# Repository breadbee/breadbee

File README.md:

# Breadbee

A very small, 32mm x 30mm, ARM Cortex A7 development board that costs about ~$10
to make in low quantities and can be assembled at home with a cheap hot air rework
station. With a [small adapter socket](./hivee) it can be mounted vertically in a standard breadboard.

The breadbee is based on a relatively unknown IP camera SoC, the MSC313E, from a company called MStar
(now part of MediaTek as a subsidiary called SigmaStar).
You might have never heard of MStar but you probably have one of their chips in your TV.

## Features

These are features that are working:

- ~1GHz Cortex A7 CPU with NEON etc[0].
- 64MB DDR2 (Probably DDR2-1333)
- 128KB SRAM (88KB if you use a MSC313(no e).
- [Bootable, memory mapped SPI-NOR](https://github.com/fifteenhex/linux/blob/msc313e/drivers/spi/spi-msc313-isp.c)
- 100Mbit ethernet.
- [4 x 10bit ADC channels](https://github.com/fifteenhex/linux/blob/msc313e/drivers/iio/adc/msc313e_sar.c)
- [2 x SPI](https://github.com/fifteenhex/linux/blob/msc313e/drivers/spi/spi-msc313.c)
- [1 x I2C (there is possibly one more)](https://github.com/fifteenhex/linux/blob/msc313e/drivers/i2c/busses/i2c-msc313e.c)
- [3 UARTs](https://github.com/fifteenhex/linux/blob/b3c521f8f30c9cc6f9f9c5c87429336d4756dcca/drivers/tty/serial/8250/8250_dw.c#L751) [1]
- Lots of GPIO. At least one pin with wake up support.
- [RTC](https://github.com/fifteenhex/linux/blob/msc313e/drivers/rtc/rtc-msc313e.c)
- [WDT](https://github.com/fifteenhex/linux/blob/msc313e/drivers/watchdog/msc313e_wdt.c)
- [3 x Timer](https://github.com/fifteenhex/linux/blob/msc313e/drivers/clocksource/timer-msc313e.c)
- [8 x PWM](https://github.com/fifteenhex/linux/blob/msc313e/drivers/pwm/pwm-msc313e.c)
- [SD/SDIO interface](https://github.com/fifteenhex/linux/blob/msc313e/drivers/mmc/host/mstar-fcie.c)
- 2 x ["byte" dma controller](https://github.com/fifteenhex/linux/blob/msc313e/drivers/dma/mstar/mstar-msc313-bdma.c)
- USB PHY
- USB host/device mux
- Faraday FUSBH200 USB *ehci* host controller
- On die temperature sensor. (sorta)
- Hardware RNG. (quality unknown)
- SHA engine. (Runs, not wired to the kernel)
- 8051 "house keeping" MCU. (Basic remoteproc driver)

[0] MStar says it's 800MHz but their own cpufreq code says they clock it to 1GHz
Clocking up to 1.1GHz works fine running dhrystone for hours but causes random lock ups if the spi nor controller and ethernet are fighting for bus access.
[1] One UART is used by the serial console, two more are available via muxing. 

 The chip has a bunch of stuff in it that isn't supported yet:
 - [MUSB USB device controller](https://github.com/fifteenhex/linux/blob/msc313e/drivers/usb/musb/mstar.c)
 - Camera interface, h264 encoder, mjpeg etc.
 - Audio ADC/DAC
 - [Crypto engine](https://github.com/fifteenhex/linux/blob/msc313e/drivers/crypto/msc313-aesdma.c) that seems to be able to do AES encrypted DMA transfers, memory mapped AES encryption etc
 - Some sort of IR decoder that can wake the chip up based on the IR codes it sees.
 - 6 byte unique device ID and efuse for key storage
 - [command queue dma controller](https://github.com/fifteenhex/linux/blob/msc313e/drivers/dma/mstar/mstar-msc313-cmdq.c)

It's full of flashy magic!

## Power consumption

According to a Kyoritsu KEW 1062 inline with the vbus of a usb cable:

| state        | Ethernet on | RTC wake | value |
|--------------|-------------|----------|-------|
| Booted idle  | yes         | N/A      | 138mA |
| Booted idle  | no          | N/A      | 113mA |
| Memory sleep |             | Yes      | 12mA  |

## Board Revisions

- Rev0 - Original version, works.
- Rev1 - Same as rev0 basically but the QFN80 footprint is slightly fixed to not have very thin pads on one side. Rev1 has one weird pad on the QFN80 footprint and an overlapping extra trace on one of the USB signals.

## Motivations

- Networked microcontrollers are a disaster waiting to happen; Many solutions - even commercial ones - use LWIP as the TCP/IP stack with no intention of actually maintaining it, use relatively unknown TLS libraries because of lack of memory, have no memory protection, no isolation between the moving parts.

- There are no solutions yet that can run a real OS like Linux that can be integrated by hobbyists into boards from cheap PCB vendors that don't have show stopping limitations. I.e. the AllWinner V3s is very similar to the SoC used here but it only has one SPI controller that is lost as soon as you put SPI NOR on it. The MSC313E has just enough of the usual microcontroller peripherals to make it useful, comes in a (relatively) easy to work with QFN package, is tiny and costs ~$4.
It is a bit harder to integrate into your designs than a microcontroller that requires a single power supply but all of the information you would need to do so is right here. The schematic for the breadbee is incredibly simple.

- There are single board computers out there that have more cores, more memory etc and are still around $10 but they are over kill for applications where even an ESP32 has enough horse power and they aren't usually something you can integrate into your project without reserving considerable space.

- Why not? The MSC313E is a Cortex-A so getting Linux running from scratch was relatively simple. The peripherals are super weird in places but not totally insane.

## But where's the WiFi!>!!111

The breadbee is meant to be a "minimum viable product" to get the ball rolling. It's impossible to write drivers for the SDIO controller or USB needed for WiFi without a platform to work on. Breadbee is that platform. Once SDIO works there will be an Ampak AP6212 based module to add wifi to breadbees and maybe a respin of the breadbee with the ethernet jack replaced with an Ampak module. 

A simpler alternative consists in using an already supported USB-to-WiFi PCB module given that the breadbee's USB host controller already works fine. This project is .

## Can I have one.. where do I get the chips..

- If you ask very nicely and you are willing to do something like write a nice python library or flesh out drivers for the board it's possible you can have one of the prototype boards for FREE! Get in touch!

- ~~If you just want to buy one the intention is to put the board up on a crowd sourcing site at some point. When that happens that information will be here.~~ [crowdsupply](https://www.crowdsupply.com/daniel-palmer/breadbee) will eventually be selling premade boards. This might take a while though.

- If you want chips to integrate into your own projects and don't have contacts in Shenzhen to get them get in touch and we'll figure something out. If you want 2080 of them getting them isn't a problem. If you want one or two I have a small supply. If the crowd sourcing happens and there is enough money left to buy extra chips to distribute in more accessible ways I will. Since April 2020 chips have now also started to turn on up ebay.

- The gerbers have been uploaded to [OSH park (rev1)](https://oshpark.com/shared_projects/lQ6wt3Dk) ready to order. [OSH park (rev0)](https://oshpark.com/shared_projects/slorKWK0)

## Software

Note that this is all in flux right at the moment. These repos are getting rebase'd fairly often.

### U-boot

There is a basic port of u-boot that so far take over from the MStar IPL and load a kernel from the SPI NOR, write it etc.
See boot process below for more details.

https://github.com/fifteenhex/u-boot/tree/msc313

### Kernel

All of the above features work to some degree in the work tree. Mainlining is in progress but will take time.
For more info please see the linux-chenxing.org [page about mainlining](http://linux-chenxing.org/mainlining.html).

### Buildroot

Combines the u-boot and kernel above with a root filesystem and generates flashable images.
There are some small pieces of a board configuration application called "beecfg" to setup pinmuxing etc.

https://github.com/fifteenhex/breadbee_buildroot

## BoM

[Google Sheet](https://docs.google.com/spreadsheets/d/1FwoQdfAULd6vKPnkrVnFDfQQs8OdsqdwefH3aLVehPo)

## Pin Table

### J2 - Main 2.54mm header

| interrupt | 5v tolerant |   notes   | alt functions           |    name   |  # |  # |   name    | alt functions           |   notes                 | 5v tolerant | interrupt |
|-----------|-------------|-----------|-------------------------|-----------|----|----|-----------|-------------------------|-------------------------|-------------|-----------|
|           |             |           |                         |    +5v    |  1 | 2  |   +3v3    |                         |                         |             |           |
|           |             |           |                         |    gnd    |  3 | 4  | pm_gpio4  |                         | [0]                     |    yes      |   yes     |
|           |             |           |                         | i2c1_scl  |  5 | 6  | i2c1_sda  |                         |                         |             |           |
|   yes     |             |           | ej_tck, pwm4            | spi0_cz   |  7 | 8  | spi0_ck   | ej_tms, pwm5            |                         |             |   yes     |
|   yes     |             |           | ej_tdo, pwm6            | spi0_di   |  9 | 10 | spi0_do   | ej_tdi, pwm7            |                         |             |   yes     |
|           |     yes     |           |                         | sar_gpio2 | 11 | 12 | sar_gpio3 |                         |                         |    yes      |           |
|           |     yes     |           |                         | sar_gpio1 | 13 | 14 | sar_gpio0 |                         |                         |    yes      |           |
|           |     yes     |   cs      | spi0_cz, pwm0           | fuart_rx  | 15 | 16 | fuart_tx  | spi0_ck, pwm1           |   clk                   |    yes      |           |
|           |     yes     | mosi, [1] | spi0_di, pwm2, uart1_rx | fuart_cts | 17 | 18 | fuart_rts | spi0_do, pwm3, uart1_tx |   miso                  |    yes      |           |
|           |             |           |                         | sr_io7    | 19 | 20 | sr_io6    |                         |                         |             |           |
|           |             |           |                         | sr_io5    | 21 | 22 | sr_io4    |                         |                         |             |           |
|           |             |           |                         | sr_io3    | 23 | 24 | sr_io2    |                         |                         |             |           |

0: This is a special pin that has to be explictly unlocked to be set. It seems to be intended for powering down the main CPU. It might move on rev1.

1 - When fuart is mux'd in it's also possible to mux'in uart1 and get a working rx only
    second uart here.

### J4 - Misc/High speed interfaces

* Note the USB and SD/SDIO are not guaranteed to work as literally no care was taken to route those signals properly on rev0. 

| name      | #  | alt functions | 5v tolerant | interrupt | notes |
|-----------|----|---------------|-------------|-----------|-------|
| +3v3      | 1  |               |             |           |       |
| sd_d3     | 2  |   spi1_do     | yes         |           | miso  |
| sd_d2     | 3  |   spi1_di     | yes         |           | mosi  |
| sd_d1     | 4  |   spi1_ck     | yes         |           | clk   |
| sd_d0     | 5  |   spi1_cz     | yes         |           | cs    |
| sd_cmd    | 6  |               | yes         |           |       |
| sd_clk    | 7  |               | yes         |           |       |
| pm_sd_cdz | 8  |               |             | yes       |       |
| gnd       | 9  |               |             |           |       |
| +5v       | 10 |               |             |           |       |
| usb_dm    | 11 |               |             |           |       |
| usb_dp    | 12 |               |             |           |       |
| gnd       | 13 |               |             |           |       |
| sr_io15   | 14 |               |             |           |       |
| sr_io14   | 15 |               |             |           |       |
| sr_io13   | 16 |               |             |           |       |
| sr_io12   | 17 |               |             |           |       |
| sr_io11   | 18 |               |             |           |       |
| sr_io10   | 19 |               |             |           |       |
| sr_io9    | 20 |               |             |           |       |
| sr_io8    | 21 |               |             |           |       |

### Test Points

- The audio pins are broken out to a series of test points on the left side of the parts size of the board.
- pm_irin is broken out to a test point on the ethernet jack side of the board.

## Using JTAG

JTAG is enabled at boot up on the spi0 pins by the u-boot SPL.

## More technical info

[linux-chenxing](http://linux-chenxing.org) has more info about mstar/sigmastar socs.

## Articles etc

[A nice blog entry from Willy about his experience building boards](https://wtarreau.blogspot.com/2020/09/breadbee-build-your-own-single-board.html)

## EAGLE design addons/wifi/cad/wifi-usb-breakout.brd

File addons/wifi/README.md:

# How to simply add WiFi to a breadbee

This is far from being of high quality, but provided little effort, it is possible to add a simple WiFi module to the breadbee.

There are a wide variety of cheap USB modules provided as a small 12.3x13mm PCB with 4 pins on one side and 2 on the other one. These modules work from 3.3V and are connected via USB. Usually they do not have any antenna but one can be connected to the two pins on one side.

Such modules are widely used in WiFi cameras and various consumer appliances, and are usually available from $1.50 to $5.00 depending on the modules. Just search for RTL8188EUS, RTL8188ETV, RTL8188FTV, MT7601U to find a few such devices. Most of them use the exact same footprint and pinout.

The breadbee board features a USB 2.0 controller with a port accessible on the J4 connector:

Pin |  Function
----|-----------
  1 |   +3.3V
 11 |   USB-DM
 12 |   USB-DP
 13 |   GND

Modules which contain a connector can be directly connected to these pins using 4 wires, as shown below:

In order to get a cleaner assembly, it is recommended instead to build a breakout board for the module. This is what is proposed in this directory.

The board was designed using Eagle CAD, for which the files are available in the  but the schematic and board layout are also provided as PDF and PNG in the . The board contains a PCB-printed antenna. These antennas can be efficient but are quite complex to design because they depend on the PCB's material and thickness, and the surrounding metal parts. There is a widely available literature on the subject but given the author had no experience there, a first quick-and-dirty attempt was made, losely inspired by the following documents after carefully studying them, and taking into account the constraints of the PCB's size and the fact that the one used here was single-sided:
 - https://www.nxp.com/docs/en/nxp/application-notes/AN11994.pdf
 - http://www.idc-online.com/technical_references/pdfs/electrical_engineering/A%20Highly%20Reliable%20Platform.pdf
 - https://www.cypress.com/documentation/application-notes/an91445-antenna-design-and-rf-layout-guidelines
 - https://www.autodesk.com/products/eagle/blog/everyday-app-note-design-efficient-antenna-rf-layout/
 - https://e2e.ti.com/support/wireless-connectivity/bluetooth/f/538/t/626343?CC2640R2F-Need-Smaller-BLE-2-4G-antenna-TI-design

The board was made using cheap 1.6mm FR4 PCB and provided great results (mesured as the ability to connect and maintain a correct TCP transfer rate at a given distance). Without any antenna, such boards barely connect more than 5-10 meters away on the same floor. With the PCB's antenna, it was possible to maintain roughly 20-25 Mbps between two different stairs.

It is important to make sure the board will be printed to the appropriate dimensions: the J4 connector has a 1mm pitch, and even a 1% error would cause 0.1mm error over 1cm and could be an issue to connect the pins while keeping the boards perfectly tight. It is wise to verify the alignment when drilling the 4 holes (0.4 to 0.5mm max):

Then the board may completely cover the J4 connector to keep wires short:

The module just needs to be soldered on 6 points. It's recommended to make sure that no contact may be made against the ground plane underneath the module. In case of doubt, a small piece of Kapton tape may be placed between the two, or the module can be kept slightly elevated during soldering.

The resulting assembly can then be pressed against the breadbee and connected using resistor tails. Alternately, it may be placed on top of the RJ45 connector using short wires. It would also be possible to place it on the SoC side, but in this case it is important to be very careful about insulation.

# Testing the board

First, the kernel needs to enable the UHCI controller. For this, a uhci0 DTB overlay should be used. The author doesn't know how to use overlays, so instead the following patch was applied to the DTS:

```
diff --git a/arch/arm/boot/dts/infinity3-msc313e-breadbee.dts b/arch/arm/boot/dts/infinity3-msc313e-breadbee.dts>
index d7445db8a388..8f5d111baca7 100644
--- a/arch/arm/boot/dts/infinity3-msc313e-breadbee.dts
+++ b/arch/arm/boot/dts/infinity3-msc313e-breadbee.dts
@@ -24,3 +24,7 @@ chosen {
 &pm_uart {
 	status = "okay";
 };
+
+&uhc0 {
+	status = "okay";
+};

```

From this point, the USB controller should be enumerated with its I/O memory address:
```
# dmesg | grep hcd
[    0.921383] fotg210_hcd: FOTG210 Host Controller (EHCI) Driver
[    0.934328] fotg210-hcd 1f284800.uhc: Faraday USB2.0 Host Controller
[    0.940675] fotg210-hcd 1f284800.uhc: new USB bus registered, assigned bus number 1
[    0.948413] fotg210-hcd 1f284800.uhc: irq 48, io mem 0x1f284800
[    0.962221] fotg210-hcd 1f284800.uhc: USB 2.0 started, EHCI 1.00
[    1.397675] usb 1-1: new high-speed USB device number 2 using fotg210-hcd
[   15.032213] usb 1-1: reset high-speed USB device number 2 using fotg210-hcd
```

Using `usb-devices` it should be possible to enumerate the device:

```
# /etc/bin/usb-devices 

T:  Bus=01 Lev=00 Prnt=00 Port=00 Cnt=00 Dev#=  1 Spd=480 MxCh= 1
D:  Ver= 2.00 Cls=09(hub  ) Sub=00 Prot=01 MxPS=64 #Cfgs=  1
P:  Vendor=1d6b ProdID=0002 Rev=05.08
S:  Manufacturer=Linux 5.8.1-bbw fotg210_hcd
S:  Product=Faraday USB2.0 Host Controller
S:  SerialNumber=1f284800.uhc
C:  #Ifs= 1 Cfg#= 1 Atr=e0 MxPwr=0mA
I:  If#=0x0 Alt= 0 #EPs= 1 Cls=09(hub  ) Sub=00 Prot=00 Driver=hub

T:  Bus=01 Lev=01 Prnt=01 Port=00 Cnt=01 Dev#=  2 Spd=480 MxCh= 0
D:  Ver= 2.01 Cls=00(>ifc ) Sub=00 Prot=00 MxPS=64 #Cfgs=  1
P:  Vendor=148f ProdID=7601 Rev=00.00
C:  #Ifs= 1 Cfg#= 1 Atr=80 MxPwr=160mA
I:  If#=0x0 Alt= 0 #EPs= 8 Cls=ff(vend.) Sub=ff Prot=ff Driver=mt7601u
```

Note that this is with an MT7601U board above. An RTL8188 will likely show something different. If this works, we can go on with enabling WiFi client support in the kernel.

# Enabling WiFi support in the kernel

The following config options were added on top of a kernel 5.8 config that was operational for the breadbee board. Note that we're speaking about the breadbee development tree, not yet 100% mainline. Only MT7601 was added there. Another option is available for RTL8188, but was not tested (look for `R8188EU`).

```
CONFIG_SYSTEM_DATA_VERIFICATION=y
CONFIG_ASN1=y
CONFIG_WIRELESS=y
CONFIG_CFG80211=y
CONFIG_CFG80211_REQUIRE_SIGNED_REGDB=y
CONFIG_CFG80211_USE_KERNEL_REGDB_KEYS=y
CONFIG_CFG80211_CRDA_SUPPORT=y
CONFIG_MAC80211=m
CONFIG_MAC80211_HAS_RC=y
CONFIG_MAC80211_RC_MINSTREL=y
CONFIG_MAC80211_RC_DEFAULT_MINSTREL=y
CONFIG_MAC80211_RC_DEFAULT="minstrel_ht"
CONFIG_MAC80211_LEDS=y
CONFIG_MAC80211_STA_HASH_MAX_SIZE=0
CONFIG_FW_LOADER_PAGED_BUF=y
CONFIG_EXTRA_FIRMWARE="mt7601u.bin"
CONFIG_EXTRA_FIRMWARE_DIR="/lib/firmware"
CONFIG_FW_LOADER_USER_HELPER=y
CONFIG_WLAN=y
CONFIG_WLAN_VENDOR_MEDIATEK=y
CONFIG_MT7601U=m
CONFIG_KEYS=y
CONFIG_CRYPTO_AEAD=m
CONFIG_CRYPTO_AKCIPHER=y
CONFIG_CRYPTO_GF128MUL=m
CONFIG_CRYPTO_NULL=m
CONFIG_CRYPTO_RSA=y
CONFIG_CRYPTO_CCM=m
CONFIG_CRYPTO_GCM=m
CONFIG_CRYPTO_CTR=m
CONFIG_CRYPTO_CMAC=m
CONFIG_CRYPTO_GHASH=m
CONFIG_CRYPTO_HASH_INFO=y
CONFIG_CRYPTO_LIB_ARC4=m
CONFIG_ASYMMETRIC_KEY_TYPE=y
CONFIG_ASYMMETRIC_PUBLIC_KEY_SUBTYPE=y
CONFIG_X509_CERTIFICATE_PARSER=y
CONFIG_PKCS7_MESSAGE_PARSER=y
CONFIG_SYSTEM_TRUSTED_KEYRING=y
CONFIG_SYSTEM_TRUSTED_KEYS=""
CONFIG_ASSOCIATIVE_ARRAY=y
CONFIG_CLZ_TAB=y
CONFIG_MPILIB=y
CONFIG_OID_REGISTRY=y
```

The MT7601U driver requires a firmware (`mt7601u.bin`). As there was no convenient place to store this firmware in the image, it was simply embedded in the kernel and retrieved from /lib/firmware on the build host.

Once rebuilt with these options, the kernel may be booted again and the module loaded:

```
# modprobe mt7601u
# lsmod
Module                  Size  Used by
mt7601u                45056  -2
mac80211              274432  -2
libarc4                16384  -2
```

Note the use count of -2 which was not yet diagnosed. Either it results from one of the module options to explicitly prevent from unloading the module, or it's a bug. As such if a new module option is needed, one needs to reboot the board and try again. Regardless, once the module is loaded, it works pretty fine.

# Building a stripped down wpa_supplicant

If one wants to connect to a WPA-protected network (which is very likely), the `wpa_supplicant` utility will be needed. This one will usually be huge by default as it supports a lot of protocols and options. However it also supports disabling many of them to reduce its footprint. It may be configured this way:

```
$ printf \
        "CONFIG_DRIVER_NL80211=y\n"             \
        "CONFIG_READLINE=y\n"                   \
        "CONFIG_NO_STDOUT_DEBUG=y\n"            \
        "CONFIG_NO_SCAN_PROCESSING=y\n"         \
        "CONFIG_BACKEND=file\n"                 \
        "CONFIG_NO_CONFIG_WRITE=y\n"            \
        "CONFIG_NO_CONFIG_BLOBS=y\n"            \
        "CONFIG_NO_LINUX_PACKET_SOCKET_WAR=y\n" \
        "CONFIG_IEEE80211W=y\n"                 \
        "CONFIG_NO_RANDOM_POOL=y\n"             \
        "CONFIG_GETRANDOM=y\n"                  \
        "CONFIG_IEEE80211N=y\n"                 \
        "CONFIG_IEEE80211AC=y\n"                \
        "CONFIG_NO_ROAMING=y\n"                 \
        "CONFIG_IBSS_RSN=y\n"                   \
        > wpa_supplicant/.config

$ CC=/path/to/cross-compiler LD='$(CC)' CFLAGS="-MMD -Os" \
  make -j$(nproc) -C wpa_supplicant
```

The development version of openssl and libnl will have to be installed in the sysroot. The resulting binary is still large (~300 kB) but compresses well in a squashfs (~120 kB).

A minimal config file like this one is sufficient:

```
# cat /etc/wpa_supplicant-wlan0.conf
network={
 ssid="lab-test"
 scan_ssid=1
 key_mgmt=WPA-PSK
 proto=WPA RSN
 psk="Lab-Test-Passw0rd"
}
```

Starting wpa_supplicant with the wlan0 interface using this config should now work:

```
# wpa_supplicant -B -iwlan0 -c/etc/wpa_supplicant-wlan0.conf -P/var/run/wpa_supplicant-wlan0.pid
# iw dev
phy#0
 Interface wlan0
   ifindex 3
   wdev 0x1
   addr 00:0c:43:12:34:56
   ssid lab-test
   type managed
   channel 7 (2442 MHz), width: 40 MHz, center1: 2452 MHz
   txpower 20.00 dBm

```

Once this is done, the wlan0 interface should appear as `UP` and an address may be retrieved using dhcpcd:

```
# ip li show dev wlan0
3: wlan0: <BROADCAST,MULTICAST,UP,LOWER_UP> mtu 1500 qdisc mq state UP mode DORMANT group default qlen 1000
    link/ether 00:0c:43:12:34:56 brd ff:ff:ff:ff:ff:ff
```

From now on, everything is specific to the distro in use.

# Final words

It's very easy to add such a module that might be salvaged from a dead camera (like the one used above), and the breadbee has the excellent taste of placing the pins in the same order as the module's so there's no risk of getting anything wrong. The breakout board is not strictly required, a previous successful attempt was made using 3cm wires on both the `ANT` and `GND` pins that were bent over the RJ45 connector. As a side note, this howto was written with dumps retrieved from the breadbee over Wifi! Try it, it's easy and fun. You won't look at your ESP32 the same way after that :-) Happy hacking with the breadbee!

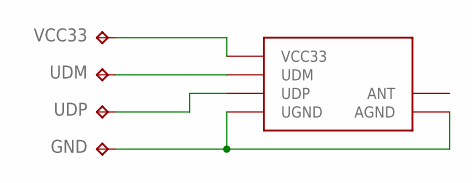
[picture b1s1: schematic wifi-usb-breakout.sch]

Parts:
GND: TPTP09R; TP09R
U$1: USB-WIFI-MODULE
UDM: TPTP09R; TP09R
UDP: TPTP09R; TP09R
VCC33: TPTP09R; TP09R

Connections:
unnamed: U$1.P$1 (VCC33), VCC33.TP
unnamed: U$1.P$2 (UDM), UDM.TP
unnamed: U$1.P$3 (UDP), UDP.TP
unnamed: GND.TP, U$1.P$4 (UGND), U$1.P$5 (AGND)

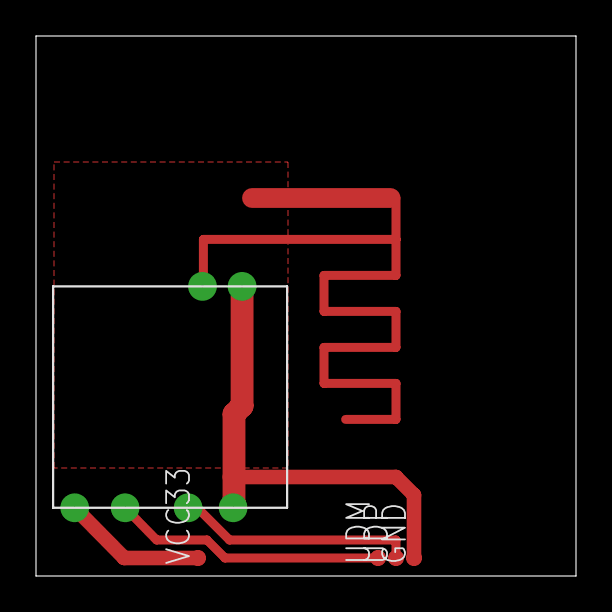
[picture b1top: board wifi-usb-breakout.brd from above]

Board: 2 copper layers, 30.0 x 30.0 mm, 5 parts (0 on the bottom side), 4 nets.

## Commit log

2019-05-13 rev0: renders
2019-05-24 rev0
2019-05-24 Everyone loves a readme
2019-05-24 Add pin table for j2
2019-05-30 Fix some component values
2019-06-10 Add layout file for flashrom used to replace firmware bits. Add openocd config file.
2019-06-14 Fix screw up with the sar pins
2019-06-15 Clean up schematic. Add PDF plot of schematic.
2019-06-18 Add a blinky gif
2019-06-19 Add hivee breadboard adapter
2019-07-09 Add scan of board
2019-07-09 Move component side board scan into sub directory
2019-07-10 Add links to relevant drivers
2019-07-10 Add small 1mm -> 2.54mm break out.
2019-09-03 USB SDIO io breakout
2019-09-03 Fix solder mask.
2019-12-02 USB works now.
2020-04-14 Add link to linux-chenxing
2020-04-20 Add missing symbol/footprint tables
    The repository is missing the fp-lib-table and sym-lib-table files which
    makes problems when editing/viewing schematics on freshly cloned repo.
    The provided tables uses ${KIPRJMOD} to be independent from the path in
    the file system.
2020-04-20 pcb: fix the sloppy solder mask
2020-04-20 pcb/footprint: fix up the thin pins on the soc
2020-04-20 sch: add missing values
2020-04-20 Add the usb/sd card breakout
2020-04-23 Missing values, public bom link
2020-06-07 Move how to build
2020-06-07 rev 1+ - fix another weird pad
2020-06-07 howtobuild: images
2020-06-25 pcb: remove redundant fragment of usb_dp
    On a wire connecting the usb_dp to the header pin there was a redundant
    fragment that was going on top of the actual wire connecting the whole
    net. A small part of this wire had an offset making the wire ticker in
    one place as well.
    I noticed that by pure luck by manually going over the wire (after
    pressing I). Unfortunately I don't know any method of automatically
2020-06-25 footprints: fix courtyard of wson8-8x6mm
    One edge (left one) of the courtyard box in this package was drawn on
    the wrong layer (Dwgs.User instead of F.CrtYd) like others. While
    hard/impossible to see by an eye, for the Kicad this was unclosed shape
    making it complain in DRC if courtyard checks are enabled.
    Note that in order to make this change small and easy to merge in case
    of conflicts, I did not include the change on the kicad_pcb file after
2020-06-25 footprints: fix courtyard width on wson8-8x6mm
    While I was editing the courtyard of this footprint I noticed that it
    has a default width of 0.15mm. The Kicad Library Conventions point 5.3
    (https://kicad-pcb.org/libraries/klc/F5.3/) specifies, however, that
    courtyard with should be 0.05mm
2020-06-28 Attempting to CI this
2020-06-28 Try to use pcbdraw
2020-06-28 Use debian sid
2020-06-28 Add a makefile to render outputs
2020-06-28 Publish the rendered files
2020-07-04 howtobuild: provide a printable reference for components
    This adds:
    - components-layout.svg : source file (inkscape)
    - components-only.pdf : components only, printable format
    - components-copper.jpg : components on top of copper tracks
    - components-photo.jpg : components on top of finished board photo
    howtobuild was updated to mention it.
2020-07-11 howtobuild: update the components layout
    - D2 (top left) is the yellow LED
    - D1 (right) is the red LED
    Also added locations of a few reference voltages to ease debugging.
2020-08-18 Add swanky ibom
2020-08-22 Move the addons out into their own repo: https://github.com/breadbee/breadbee_addons
2020-08-24 addons: add info about how to easily add a cheap WiFi module
    It's particularly easy to add WiFi support to the breadbee, so let's
    document how this can be done, providing configs, patches, schematics,
    boards and photos.
2020-08-24 addons: Fix a minor typo.
